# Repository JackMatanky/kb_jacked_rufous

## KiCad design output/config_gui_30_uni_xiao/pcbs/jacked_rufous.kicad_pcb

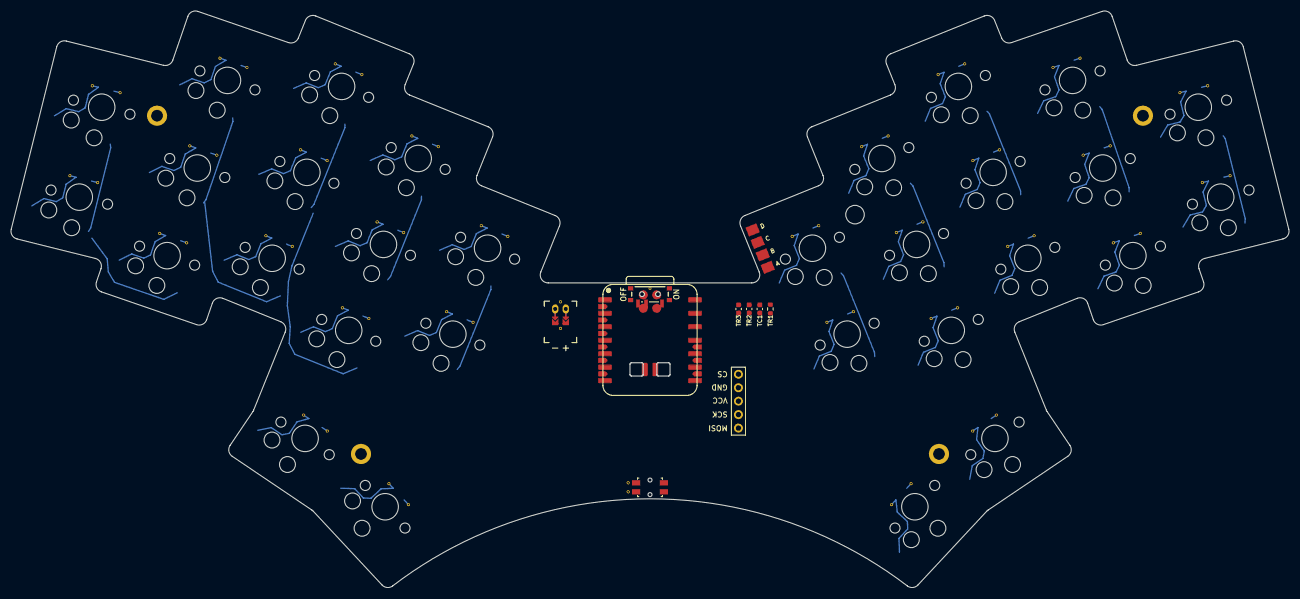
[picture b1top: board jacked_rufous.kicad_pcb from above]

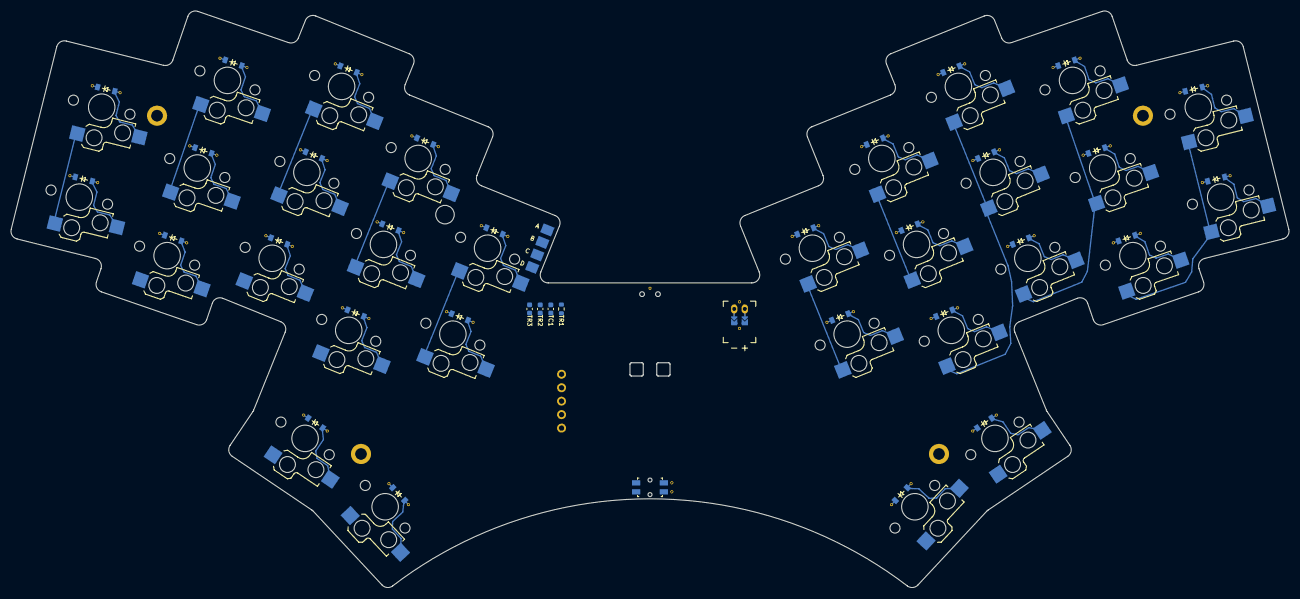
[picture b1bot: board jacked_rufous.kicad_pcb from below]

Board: 2 copper layers, 241.3 x 108.9 mm, 71 parts (60 on the bottom side), 40 nets.

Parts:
D1, D2, D3, D4, D5, D6, D7, D8, D9, D10, D11, D12, D13, D14, D15, D16, D17, D18, D19, D20, D21, D22, D23, D24, D25, D26, D27, D28, D29, D30: diode_tht_sod123
DISP1: display_nice_view
H1, H2, H3, H4: mounting_hole_plated
JST1: battery_connector_jst_ph_2
MCU: xiao-plus
PWR1: power_switch_smd_side
RST1: reset_switch_smd_side
S1, S2, S3, S4, S5, S6, S7, S8, S9, S10, S11, S12, S13, S14, S15, S16, S17, S18, S19, S20, S21, S22, S23, S24, S25, S26, S27, S28, S29, S30: switch_choc_v1_v2
TP1: trackpoint_t460s_stick
TR1: trackpoint_reset

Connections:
C1: MCU.5, S1.1, S2.1, S3.1, S14.1, S15.1, S16.1
C2: MCU.6, S4.1, S5.1, S6.1, S17.1, S18.1, S19.1
C3: MCU.7, S7.1, S8.1, S9.1, S20.1, S21.1, S22.1
C4: MCU.8, S10.1, S11.1, S23.1, S24.1, S27.1, S29.1
C5: MCU.15, S12.1, S13.1, S25.1, S26.1, S28.1, S30.1
CS: DISP1.5, MCU.10
GND: DISP1.4, JST1.2, MCU.13, MCU.27, MCU.33, RST1.1, RST1.3, TP1.B, TR1.1
JST1_1: JST1.11, JST1.21, JST1.31
JST1_2: JST1.12, JST1.22, JST1.32
MOSI: DISP1.1, MCU.11
R1: D2.1, D5.1, D8.1, D11.1, D13.1, MCU.16
R2: D1.1, D4.1, D7.1, D10.1, D12.1, MCU.17
R3: D3.1, D6.1, D9.1, D27.1, D28.1, MCU.18
R4: D15.1, D18.1, D21.1, D24.1, D26.1, MCU.19
R5: D14.1, D17.1, D20.1, D23.1, D25.1, MCU.21
R6: D16.1, D19.1, D22.1, D29.1, D30.1, MCU.22
RAW: MCU.32, PWR1.2
RST: MCU.26, RST1.2, RST1.4
SCK: DISP1.2, MCU.9
TPC: MCU.2, TP1.D, TR1.8
TPD: MCU.1, TP1.C, TR1.6
TPR: TR1.2, TR1.4
VCC: DISP1.3, MCU.12, TP1.A, TR1.3, TR1.5, TR1.7
c1_r1: D2.2, S2.2
c1_r2: D1.2, S1.2
c2_r1: D5.2, S5.2
c2_r2: D4.2, S4.2
c2_r3: D3.2, S3.2
c3_r1: D8.2, S8.2
c3_r2: D7.2, S7.2
c3_r3: D6.2, S6.2
c4_r1: D11.2, S11.2
c4_r2: D10.2, S10.2
c4_r3: D9.2, S9.2
c5_r1: D13.2, S13.2
c5_r2: D12.2, S12.2
in_home: D28.2, S28.2
mirror_mirror_{{col.name}}_{{row}}: D14.2, D15.2, D16.2, D17.2, D18.2, D19.2, D20.2, D21.2, D22.2, D23.2, D24.2, D25.2, D26.2, D29.2, D30.2, S14.2, S15.2, S16.2, S17.2, S18.2, S19.2, S20.2, S21.2, S22.2, S23.2, S24.2, S25.2, S26.2, S29.2, S30.2
out_home: D27.2, S27.2
pos: JST1.1, PWR1.1

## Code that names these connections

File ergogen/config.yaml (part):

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        reversible: true
        include_traces_vias: true
        pin_1: VCC
        pin_2: TPD
        pin_3: TPR
        pin_7: GND
        pin_8: TPC

    tp_reset:
      what: kb_footprints/ergogen/trackpoint_reset
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
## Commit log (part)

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2025-12-11 first commit after separating jacked rufous kb from snak
2026-01-04 update kb url and comment headers
